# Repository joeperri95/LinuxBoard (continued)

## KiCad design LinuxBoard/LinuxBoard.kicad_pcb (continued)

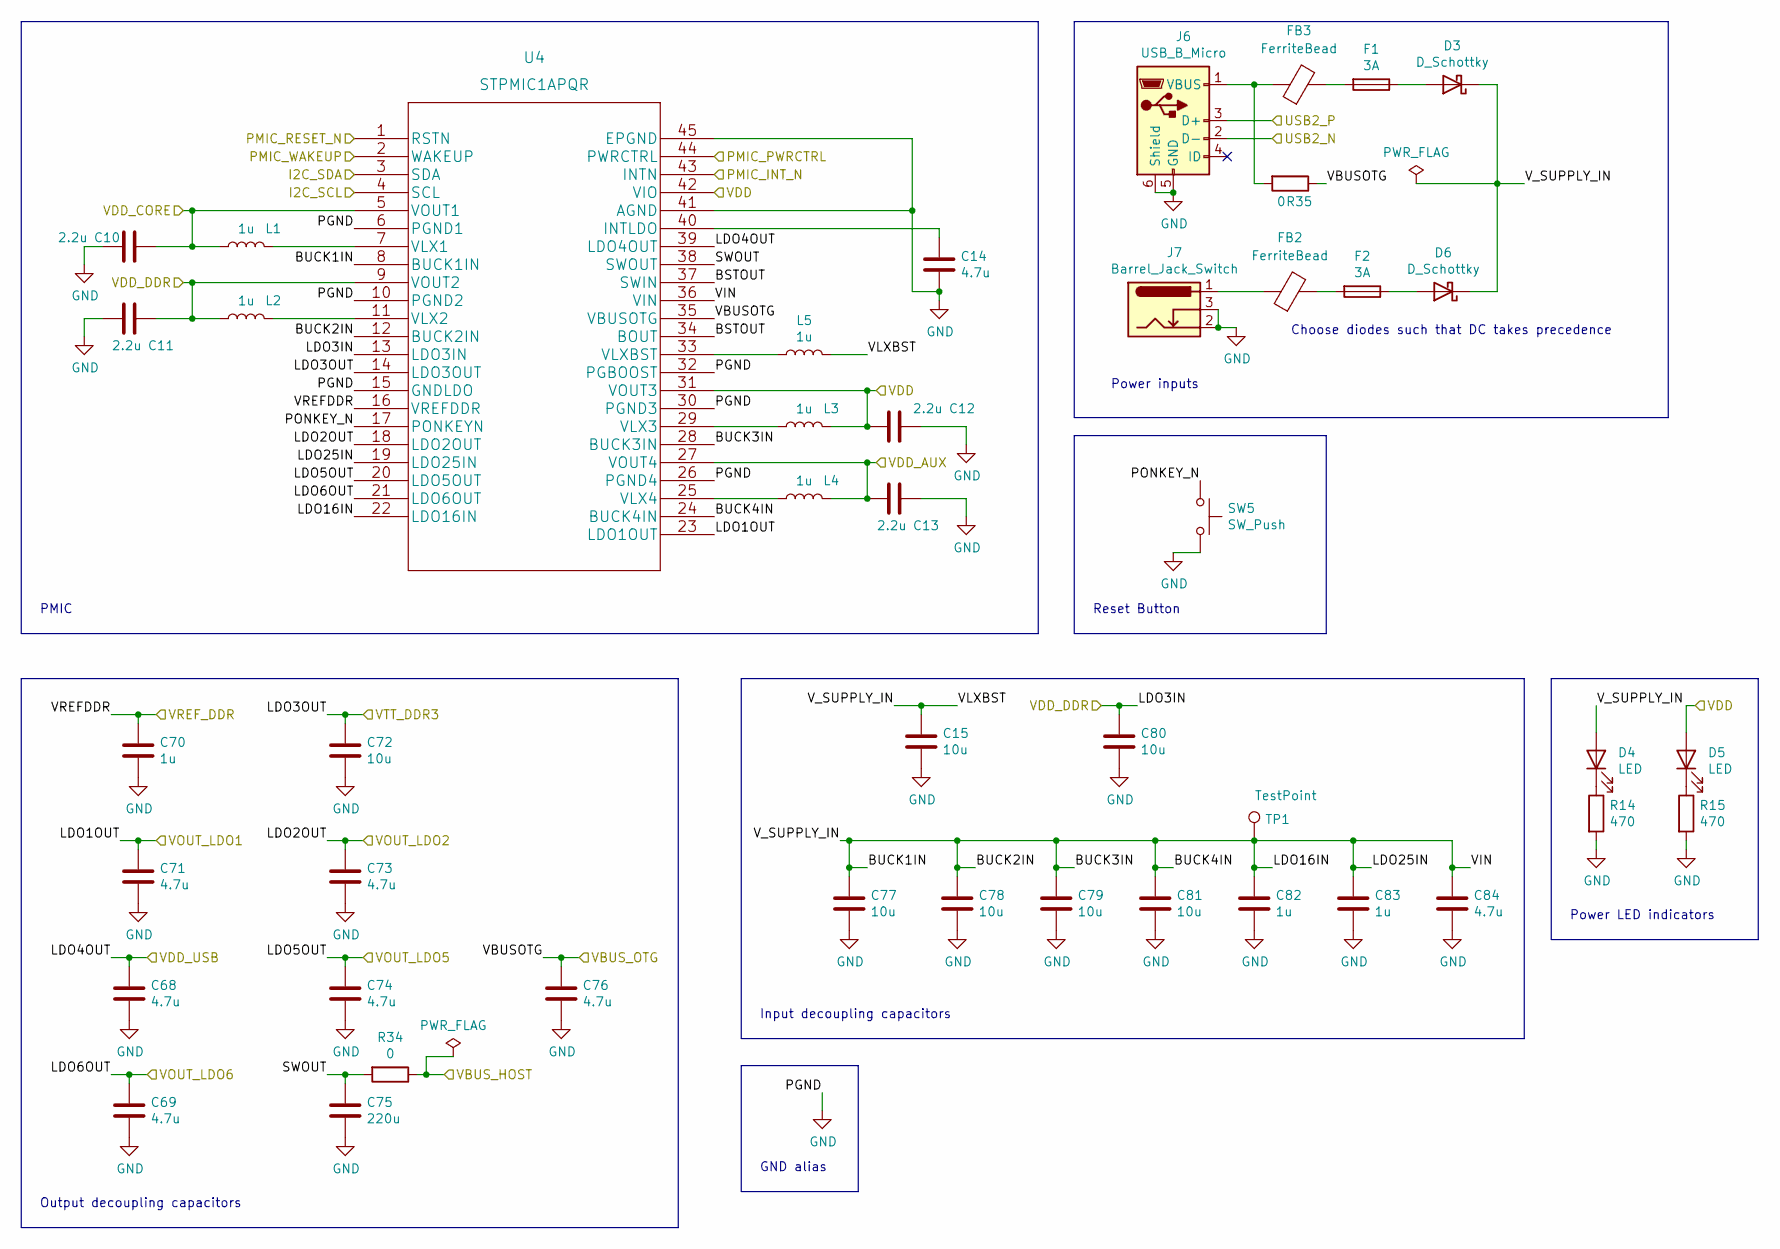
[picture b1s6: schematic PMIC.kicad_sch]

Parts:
C10, C11, C12, C13: 2.2u; C_0603_1608Metric
C14, C68, C69, C71, C73, C74, C76, C84: 4.7u; C_0603_1608Metric
C15, C72, C77, C78, C79, C80, C81: 10u; C_0603_1608Metric
C70, C82, C83: 1u; C_0603_1608Metric
C75: 220u; C_0603_1608Metric
D3, D6: D_Schottky; D_0603_1608Metric
D4, D5: LED; LED_0603_1608Metric
F1, F2: 3A; Fuse_0603_1608Metric
FB2, FB3: FerriteBead; L_0603_1608Metric_Pad1.05x0.95mm_HandSolder
J6: USB_B_Micro; USB_Micro-B_Amphenol_10103594-0001LF_Horizontal
J7: Barrel_Jack_Switch; BarrelJack_Wuerth_6941xx301002
L1, L2, L3, L4, L5: 1u; L_0603_1608Metric
R14, R15: 470; R_0603_1608Metric_Pad0.98x0.95mm_HandSolder
R34, R35: 0; R_0603_1608Metric_Pad0.98x0.95mm_HandSolder
SW5: SW_Push; SW_Push_1P1T_NO_6x6mm_H9.5mm
TP1: TestPoint; TestPoint_Pad_D2.0mm
U4: STPMIC1APQR

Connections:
/MPU/I2C_SCL: U4.4 (SCL); also elsewhere on the board
/MPU/I2C_SDA: U4.3 (SDA); also elsewhere on the board
/MPU/PMIC_INT_N: U4.43 (INTN); also elsewhere on the board
/MPU/PMIC_WAKEUP: U4.2 (WAKEUP); also elsewhere on the board
/MPU/USB2_N: J6.2 (D-); also elsewhere on the board
/MPU/USB2_P: J6.3 (D+); also elsewhere on the board
/MPU/VBUS_HOST: R34.1; also elsewhere on the board
/MPU_Power/VDDQ_DDR: C11.1, C80.1, L2.1, U4.9 (VOUT2), U4.13 (LDO3IN); also elsewhere on the board
/MPU_Power/VDD_CORE: C10.1, L1.1, U4.5 (VOUT1); also elsewhere on the board
/PMIC/BSTOUT: U4.34 (BOUT), U4.37 (SWIN)
/PMIC/BUCK1IN: C15.1, C77.1, C78.1, C79.1, C81.1, C82.1, C83.1, C84.1, D3.1 (K), D4.2 (A), D6.1 (K), L5.2, TP1.1, U4.8 (BUCK1IN), U4.12 (BUCK2IN), U4.19 (LDO25IN), U4.22 (LDO16IN), U4.24 (BUCK4IN), U4.28 (BUCK3IN), U4.36 (VIN)
/PMIC/LDO1OUT: C71.1, U4.23 (LDO1OUT); also elsewhere on the board
/PMIC/LDO2OUT: C73.1, U4.18 (LDO2OUT); also elsewhere on the board
/PMIC/LDO3OUT: C72.1, U4.14 (LDO3OUT); also elsewhere on the board
/PMIC/LDO4OUT: C68.1, U4.39 (LDO4OUT); also elsewhere on the board
/PMIC/LDO5OUT: C74.1, U4.20 (LDO5OUT); also elsewhere on the board
/PMIC/LDO6OUT: C69.1, U4.21 (LDO6OUT); also elsewhere on the board
/PMIC/PMIC_PWRCTRL: U4.44 (PWRCTRL); also elsewhere on the board
/PMIC/PONKEY_N: SW5.1, U4.17 (PONKEYN)
/PMIC/SWOUT: C75.1, R34.2, U4.38 (SWOUT)
/PMIC/VBUSOTG: C76.1, R35.1, U4.35 (VBUSOTG); also elsewhere on the board
/PMIC/VDD_AUX: C13.2, L4.2, U4.27 (VOUT4); also elsewhere on the board
/PMIC/VREFDDR: C70.1, U4.16 (VREFDDR); also elsewhere on the board
/RAM/NRST: U4.1 (RSTN); also elsewhere on the board
/VDD: C12.2, D5.2 (A), L3.2, U4.31 (VOUT3), U4.42 (VIO); also elsewhere on the board
GND: C10.2, C11.2, C12.1, C13.1, C14.2, C15.2, C68.2, C69.2, C70.2, C71.2, C72.2, C73.2, C74.2, C75.2, C76.2, C77.2, C78.2, C79.2, C80.2, C81.2, C82.2, C83.2, C84.2, J6.5 (GND), J6.6 (Shield), J7.2, J7.3, R14.2, R15.2, SW5.2, U4.6 (PGND1), U4.10 (PGND2), U4.15 (GNDLDO), U4.26 (PGND4), U4.30 (PGND3), U4.32 (PGBOOST), U4.41 (AGND), U4.45 (EPGND); also elsewhere on the board
unnamed: C14.1, U4.40 (INTLDO)
unnamed: D3.2 (A), F1.1
unnamed: D4.1 (K), R14.1
unnamed: D5.1 (K), R15.1
unnamed: D6.2 (A), F2.1
unnamed: F1.2, FB3.2
unnamed: F2.2, FB2.2
unnamed: FB2.1, J7.1
unnamed: FB3.1, J6.1 (VBUS), R35.2
unnamed: L1.2, U4.7 (VLX1)
unnamed: L2.2, U4.11 (VLX2)
unnamed: L3.1, U4.29 (VLX3)
unnamed: L4.1, U4.25 (VLX4)
unnamed: L5.1, U4.33 (VLXBST)

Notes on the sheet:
PMIC
Power LED indicators
Choose diodes such that DC takes precedence
GND alias
Reset Button
Power inputs
Input decoupling capacitors
Output decoupling capacitors

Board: 2 copper layers, 189 parts (0 on the bottom side), 173 nets, no tracks yet.

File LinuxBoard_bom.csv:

"Source:","/home/joe/Workspace/Hardware/LinuxBoard/LinuxBoard.sch"
"Date:","Fri 30 Apr 2021 09:53:23 AM"
"Tool:","Eeschema 5.1.5+dfsg1-2build2"
"Generator:","/usr/share/kicad/plugins/bom_csv_grouped_by_value_with_fp.py"
"Component Count:","180"
"Ref","Qnty","Value","Cmp name","Footprint","Description","Vendor"
"C1, C2, ","2","12p","C","Capacitor_SMD:C_0603_1608Metric","Unpolarized capacitor",""
"C3, C4, ","2","20p","C","Capacitor_SMD:C_0603_1608Metric","Unpolarized capacitor",""
"C5, C7, C9, C43, C44, C45, C58, C59, C60, C63, C64, C65, C66, C85, C86, C87, C88, C89, C90, C91, C93, ","21","100n","C","Capacitor_SMD:C_0603_1608Metric","Unpolarized capacitor",""
"C6, C8, ","2","33p","C","Capacitor_SMD:C_0603_1608Metric","Unpolarized capacitor",""
"C10, C11, C12, C13, C32, C33, ","6","2.2u","C","Capacitor_SMD:C_0603_1608Metric","Unpolarized capacitor",""
"C14, C68, C69, C71, C73, C74, C76, C84, ","8","4.7u","C","Capacitor_SMD:C_0603_1608Metric","Unpolarized capacitor",""
"C15, C57, C61, C62, C72, C77, C78, C79, C80, C81, ","10","10u","C","Capacitor_SMD:C_0603_1608Metric","Unpolarized capacitor",""
"C16, C18, C19, C20, C22, C23, C24, C25, C26, C27, C28, C29, C30, C31, C34, C35, C36, C37, C38, C39, C40, C41, C42, C46, C47, C48, C49, C50, C51, C52, C53, C54, C55, C56, C70, C82, C83, ","37","1u","C","Capacitor_SMD:C_0603_1608Metric","Unpolarized capacitor",""
"C17, C21, ","2","1n","C","Capacitor_SMD:C_0603_1608Metric","Unpolarized capacitor",""
"C67, C94, ","2","10n","C","Capacitor_SMD:C_0603_1608Metric","Unpolarized capacitor",""
"C75, ","1","220u","C","Capacitor_SMD:C_0603_1608Metric","Unpolarized capacitor",""
"C92, ","1","C","C","Capacitor_SMD:C_0603_1608Metric","Unpolarized capacitor",""
"D1, D2, D4, D5, ","4","LED","LED","LED_SMD:LED_0603_1608Metric","Light emitting diode",""
"D3, D6, ","2","D_Schottky","D_Schottky","Diode_SMD:D_0603_1608Metric","Schottky diode",""
"F1, F2, ","2","Fuse","Fuse","Fuse:Fuse_0603_1608Metric","Fuse",""
"FB1, FB2, FB4, ","3","Ferrite_Bead","Ferrite_Bead","Inductor_SMD:L_0603_1608Metric","Ferrite bead",""
"J1, ","1","Wuerth_7499010121A","Wuerth_7499010121A","Connector_RJ:RJ45_Wuerth_7499010121A_Horizontal","LAN Transformer Jack, RJ45, 10/100 BaseT",""
"J2, ","1","Conn_02x10_Counter_Clockwise","Conn_02x10_Counter_Clockwise","Connector_IDC:IDC-Header_2x10_P2.54mm_Vertical","Generic connector, double row, 02x10, counter clockwise pin numbering scheme (similar to DIP packge numbering), script generated (kicad-library-utils/schlib/autogen/connector/)",""
"J3, ","1","Micro_SD_Card","Micro_SD_Card","Connector_Card:microSD_HC_Wuerth_693072010801","Micro SD Card Socket",""
"J4, ","1","USB_A","USB_A","Connector_USB:USB_A_CNCTech_1001-011-01101_Horizontal","USB Type A connector",""
"J5, ","1","Conn_ARM_JTAG_SWD_20","Conn_ARM_JTAG_SWD_20","Connector_PinHeader_1.27mm:PinHeader_2x10_P1.27mm_Vertical","Standard IDC20 Male Connector, ARM legacy JTAG and SWD interface",""
"J6, ","1","USB_B_Micro","USB_B_Micro","Connector_USB:USB_Micro-B_Amphenol_10103594-0001LF_Horizontal","USB Micro Type B connector",""
"J7, ","1","Barrel_Jack","Barrel_Jack","","DC Barrel Jack",""
"L1, L2, L3, L4, L5, ","5","1u","L","Inductor_SMD:L_0603_1608Metric","Inductor",""
"L6, ","1","4.7u","L","Inductor_SMD:L_0603_1608Metric","Inductor",""
"R1, R2, R7, R14, R15, ","5","470","R","Resistor_SMD:R_0603_1608Metric_Pad1.05x0.95mm_HandSolder","Resistor",""
"R3, R4, R5, R18, R23, R27, R29, R32, ","8","10k","R","Resistor_SMD:R_0603_1608Metric_Pad1.05x0.95mm_HandSolder","Resistor",""
"R6, ","1","220","R","Resistor_SMD:R_0603_1608Metric_Pad1.05x0.95mm_HandSolder","Resistor",""
"R8, R21, R22, R34, R35, ","5","0","R","Resistor_SMD:R_0603_1608Metric_Pad1.05x0.95mm_HandSolder","Resistor",""
"R9, ","1","4.87K","R","Resistor_SMD:R_0603_1608Metric","Resistor",""
"R10, R11, ","2","49.9","R","Resistor_SMD:R_0603_1608Metric","Resistor",""
"R12, R13, ","2","2.2K","R","Resistor_SMD:R_0603_1608Metric","Resistor",""
"R16, ","1","220","R","Resistor_SMD:R_0603_1608Metric","Resistor",""
"R17, ","1","470","R","Resistor_SMD:R_0603_1608Metric","Resistor",""
"R19, R20, ","2","240","R","Resistor_SMD:R_0603_1608Metric","Resistor",""
"R24, R25, R26, R28, ","4","4.7k","R","Resistor_SMD:R_0603_1608Metric_Pad1.05x0.95mm_HandSolder","Resistor",""
"R30, R31, ","2","10K","R","Resistor_SMD:R_0603_1608Metric_Pad1.05x0.95mm_HandSolder","Resistor",""
"R33, ","1","3K","R","Resistor_SMD:R_0603_1608Metric","Resistor",""
"R36, ","1","DNP","R","Resistor_SMD:R_0603_1608Metric_Pad1.05x0.95mm_HandSolder","Resistor",""
"SW1, ","1","SW_DIP_x03","SW_DIP_x03","Button_Switch_SMD:SW_DIP_SPSTx03_Slide_Omron_A6S-310x_W8.9mm_P2.54mm","3x DIP Switch, Single Pole Single Throw (SPST) switch, small symbol",""
"SW2, SW3, SW4, SW5, ","4","SW_Push","SW_Push","Button_Switch_SMD:SW_Push_1P1T_NO_6x6mm_H9.5mm","Push button switch, generic, two pins",""
"TP1, TP2, TP3, TP4, TP5, TP6, TP7, TP8, TP9, TP10, TP11, TP12, TP13, TP14, ","14","TestPoint","TestPoint","TestPoint:TestPoint_Pad_D2.0mm","test point",""
"U1, ","1","STM32MP151AAB3","STM32MP151AAB3","LinuxBoard:STM32MP151AAB3","",""
"U2, ","1","MT41K64M16TW-107_AAT_J_TR","MT41K64M16TW-107_AAT_J_TR","LinuxBoard:MT41K64M16TW-107_AAT_J_TR","",""
"U3, ","1","DP83848C","DP83848C","Package_QFP:LQFP-48_7x7mm_P0.5mm","MII/RMII Single 10/100Mbps Ethernet Physical Layer Transciever, LQFP-48",""
"U4, ","1","STPMIC1APQR","STPMIC1APQR","LinuxBoard:STPMIC1APQR","",""
"Y1, ","1","24MHz","Crystal_GND24","Crystal:Crystal_SMD_2016-4Pin_2.0x1.6mm","Four pin crystal, GND on pins 2 and 4",""
"Y2, ","1","32.768KHz","Crystal","Crystal:Crystal_SMD_TXC_9HT11-2Pin_2.0x1.2mm","Two pin crystal",""
"Y3, ","1","25MHz","Crystal_GND24","Crystal:Crystal_SMD_3225-4Pin_3.2x2.5mm","Four pin crystal, GND on pins 2 and 4",""

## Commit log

2021-02-05 Add initial schematic work
2021-03-31 Add bulk labels for RAM and ethernet
2021-04-06 Add decoupling capacitors
2021-04-07 Add ddr hw guide
2021-04-12 Complete ethernet and PMIC circuitry
2021-04-12 Finish labelling RAM
2021-04-14 Finish DDR schematic
2021-04-19 Update docs
2021-04-19 Complete gpio selection, tidy sheets
2021-04-19 Add schematic pdf
2021-04-19 Remove pdf docs from repo
2021-04-21 Add DC barrel connector for alternate power supply
2021-04-27 Start crossing off ERC. Add generated BOM
2021-04-28 Add bom grouped by value
2021-04-28 Complete schematic rough draft
2021-04-30 Update footprints
2021-05-13 Update jtag connector to swd
2021-05-14 Fix footprints
2021-06-29 Add mounting holes
2021-07-08 Add termination
2021-08-11 Schematic signoff
2021-08-26 Fan out BGA
2022-01-28 Perform initial conversion
2022-02-15 Fix ERC errors and reorganize directory
2022-02-15 Fix resistor footprints, restart layout
2022-03-18 Add NXP DDR3 checklist
